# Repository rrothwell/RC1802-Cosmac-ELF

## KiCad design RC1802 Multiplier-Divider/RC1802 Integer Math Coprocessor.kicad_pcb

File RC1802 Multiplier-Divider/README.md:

# RC1802 Multiplier-Divider

This design is for a PCB card compatible with the RC1802 Cosmac ELF computer.
It uses am RCA CDP1855 integrated circuit capable of 8x8 bit integer multiplication and 16/8 division.
As of 22Feb2015 thew gerber files have been sent to manufactoruing and the PCB should be available in a week or so.

# Schematic
The supplied KiCad files should be sufficient as both a schematic and as a starting point for ordering PCBs.
Gerbers will be supplied after assembly and testing.

# BOM

The IC's seem to be readily availble on eBay, but they have yet to be tested.

Values in parenthesis is the component amounts that could be considered optional.

| Reference    | Item                                  | Count |
| ------------ | ------------------------------------- | ----- |
| PCB          | Fabricate using Gerber files  |    |

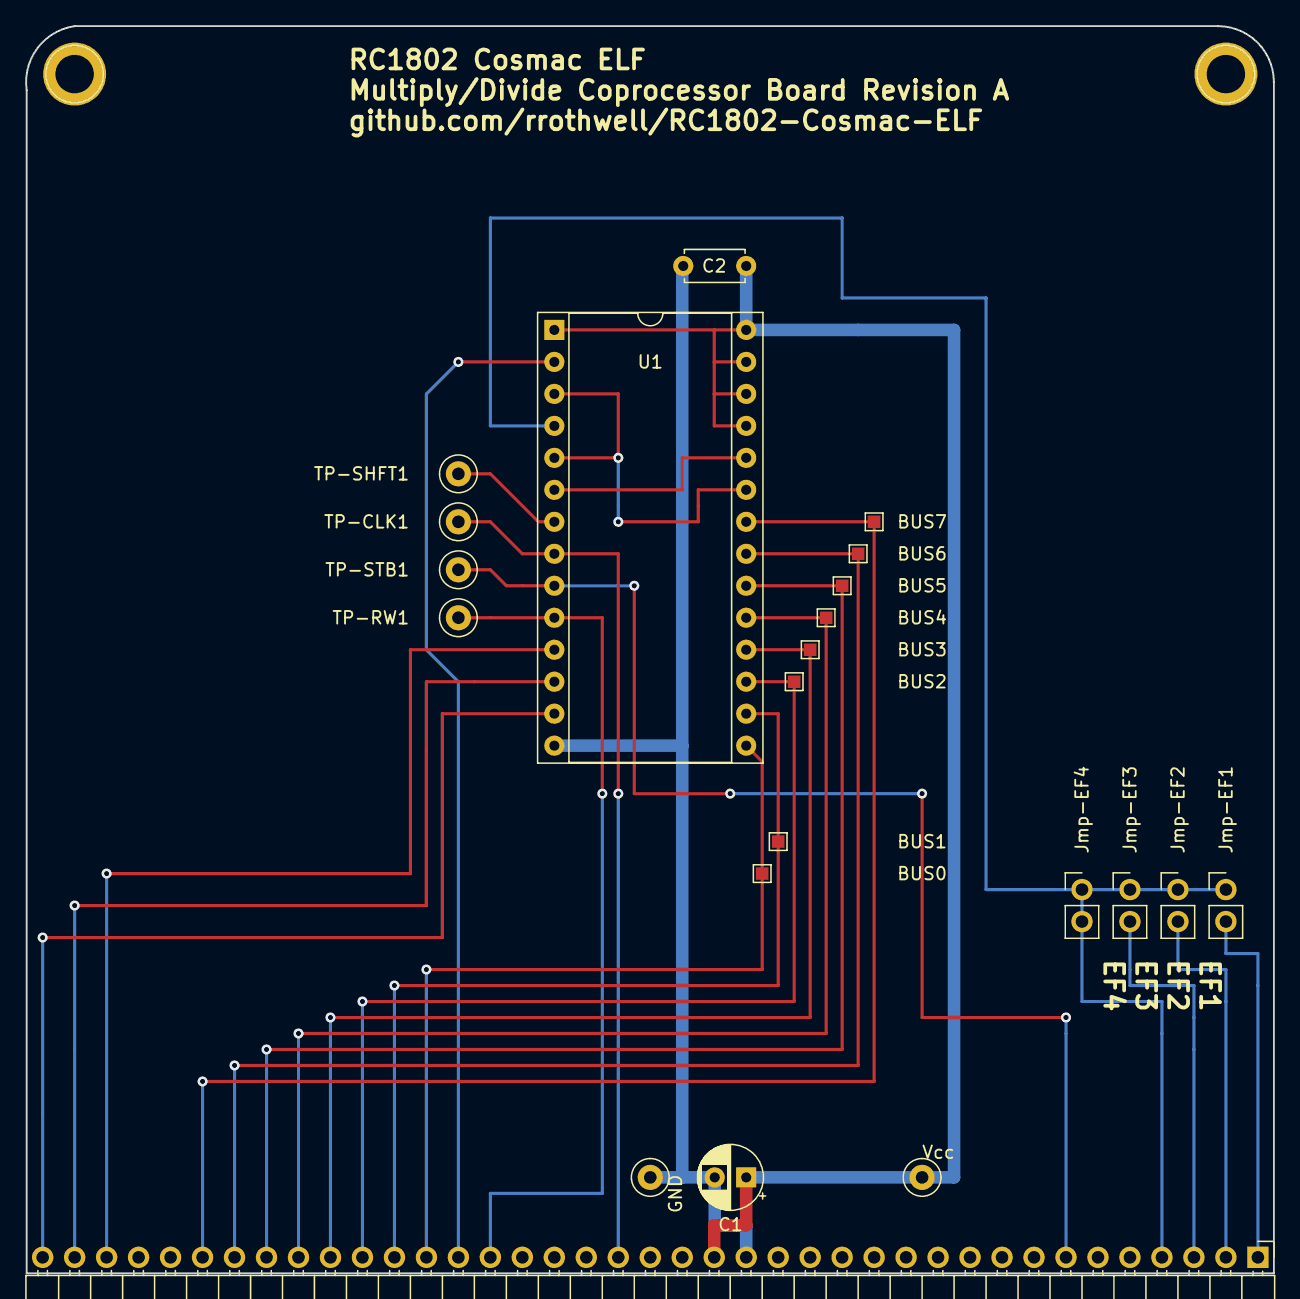
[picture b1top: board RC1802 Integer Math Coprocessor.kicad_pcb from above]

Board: 2 copper layers, 99.1 x 99.1 mm, 24 parts (0 on the bottom side), 24 nets.

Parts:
BUS0, BUS1, BUS2, BUS3, BUS4, BUS5, BUS6, BUS7: TestPoint_Small; TestPoint_Pad_1.0x1.0mm
C1: 100u; CP_Radial_D5.0mm_P2.50mm
C2: 100n; C_Disc_D4.7mm_W2.5mm_P5.00mm
GND: TestPoint_Loop_D1.80mm_Drill1.0mm_Beaded
J1: RC1802_card_edge_connector; PinHeader_1x39_P2.54mm_Horizontal
J2, J4: Mount; 1pin
Jmp-EF1, Jmp-EF2, Jmp-EF3, Jmp-EF4: PinHeader_1x02_P2.54mm_Vertical
TP-CLK1: TestPoint; TestPoint_Loop_D1.80mm_Drill1.0mm_Beaded
TP-RW1: TestPoint; TestPoint_Loop_D1.80mm_Drill1.0mm_Beaded
TP-SHFT1: TestPoint; TestPoint_Loop_D1.80mm_Drill1.0mm_Beaded
TP-STB1: TestPoint; TestPoint_Loop_D1.80mm_Drill1.0mm_Beaded
U1: CDP1855; CDP1855_Socket
Vcc: TestPoint_Loop_D1.80mm_Drill1.0mm_Beaded

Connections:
+5C: C1.1, C2.1, J1.18, U1.1, U1.25, U1.26, U1.27, U1.28, Vcc.1
GND: C1.2, C2.2, GND.1, J1.17, U1.14
unnamed: J1.4, Jmp-EF1.1, Jmp-EF2.1, Jmp-EF3.1, Jmp-EF4.1, Jmp-EF4.2, U1.4
unnamed: J1.1, Jmp-EF1.2
unnamed: J1.2, Jmp-EF2.2
unnamed: J1.3, Jmp-EF3.2
unnamed: J1.7, TP-STB1.1, U1.9
unnamed: J1.21, TP-CLK1.1, U1.8
unnamed: J1.25, TP-RW1.1, U1.10
unnamed: J1.26, U1.2
unnamed: BUS0.1, J1.27, U1.15
unnamed: BUS1.1, J1.28, U1.16
unnamed: BUS2.1, J1.29, U1.17
unnamed: BUS3.1, J1.30, U1.18
unnamed: BUS4.1, J1.31, U1.19
unnamed: BUS5.1, J1.32, U1.20
unnamed: BUS6.1, J1.33, U1.21
unnamed: BUS7.1, J1.34, U1.22
unnamed: J1.37, U1.11
unnamed: J1.38, U1.12
unnamed: J1.39, U1.13
unnamed: TP-SHFT1.1, U1.7
unnamed: U1.3, U1.5, U1.23
unnamed: U1.6, U1.24

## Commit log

2025-02-21 Initial commit of RC1802 board design for integer math coprocessor.
2025-02-25 RC1802 Multiplier-Divider/manufacturing/ Update README and commit Gerbears.
